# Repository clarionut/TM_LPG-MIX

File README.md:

# TM_LPG-MIX

This repository provides a KiCad schematic and PCB layout for a variant of the TM-LPG-X expander (https://github.com/morganmcw/TM-LPG-X) and the orignal Turing Machine Vactrol Mix expander (https://github.com/TomWhitwell/TuringMixExpander).

It includes the variation switches of the TM-LPG-X, but can be built using capacitors (LPG), resistors (Mix) or with a pin header to allow switching between LPG or Mix mode via a front panel switch (with the resistors and capacitors mounted on the switch).

In their original forms an LPG module would be connected to the Turing Machine PULSES header and a Mix module to the GATES header. This design includes a daughter board which allows both headers to be connected simultaneously. The active connection is selected by a switch or a gate voltage input (the gate input is only active when the switch is OFF).

Taken together, these features allow the unit to be built as a TM-LPG-X, a Turing Machine Vactrol Mix with variation switches, or as a fully configurable combination of the two. Experience since first completing this project has shown that the combination of home made vactrols (https://www.thingiverse.com/thing:6178403) using ultrabright red LEDs and GL5528 LDRs with 220nF capacitors for C5 and C6 leads to such a rapid decay time that the low-pass gate effect is essentially inaudible, though it is visible on an oscilloscope. Reducing the value of these capacitors to 10nF gives a decay time in the region of 0.5 - 1 second which is much more suitable for an LPG. In a similar way, the decay time in Mix mode can be increased by using resistors with a value greater than 10k in place of the capacitors. E.g. 47k resistors in Mix mode give a similar decay time to the 10nF capacitors in LPG mode. A very interesting further extension is to use a dual resistor (5k) / potentiometer (50k) combination in place of the fixed 'Mix' resistors, and a 2-pole 3- or 4-way switch to select the LPG capacitor values (e.g. 100, 33, 10 & 4.7nF) in order to make the decay time adjustable in both modes. I've now tested this ehancement and it is very much worthwhile. I used the resistor and capacitor values shown, but different values may work better depending on the characteristics of the vactrols used.

The PCB layout file uses a custom footprint for the vactrols and a custom model for the 3D viewer. There are included in the TM_LPG-MIX folder - you will have to move them to appropriate locations and tell KiCad where to find them. The PCB design is intended to be processed using the kicad-round-tracks add-on (https://github.com/mitxela/kicad-round-tracks). The schematic also includes a custom audio jack symbol, so I've included both the cache-lib file for the project and a copy of my customised symbols lbrary.

This design is Creative Commons Licensed by Chris Earnshaw: CC-BY-SA - inherited from the parent designs.

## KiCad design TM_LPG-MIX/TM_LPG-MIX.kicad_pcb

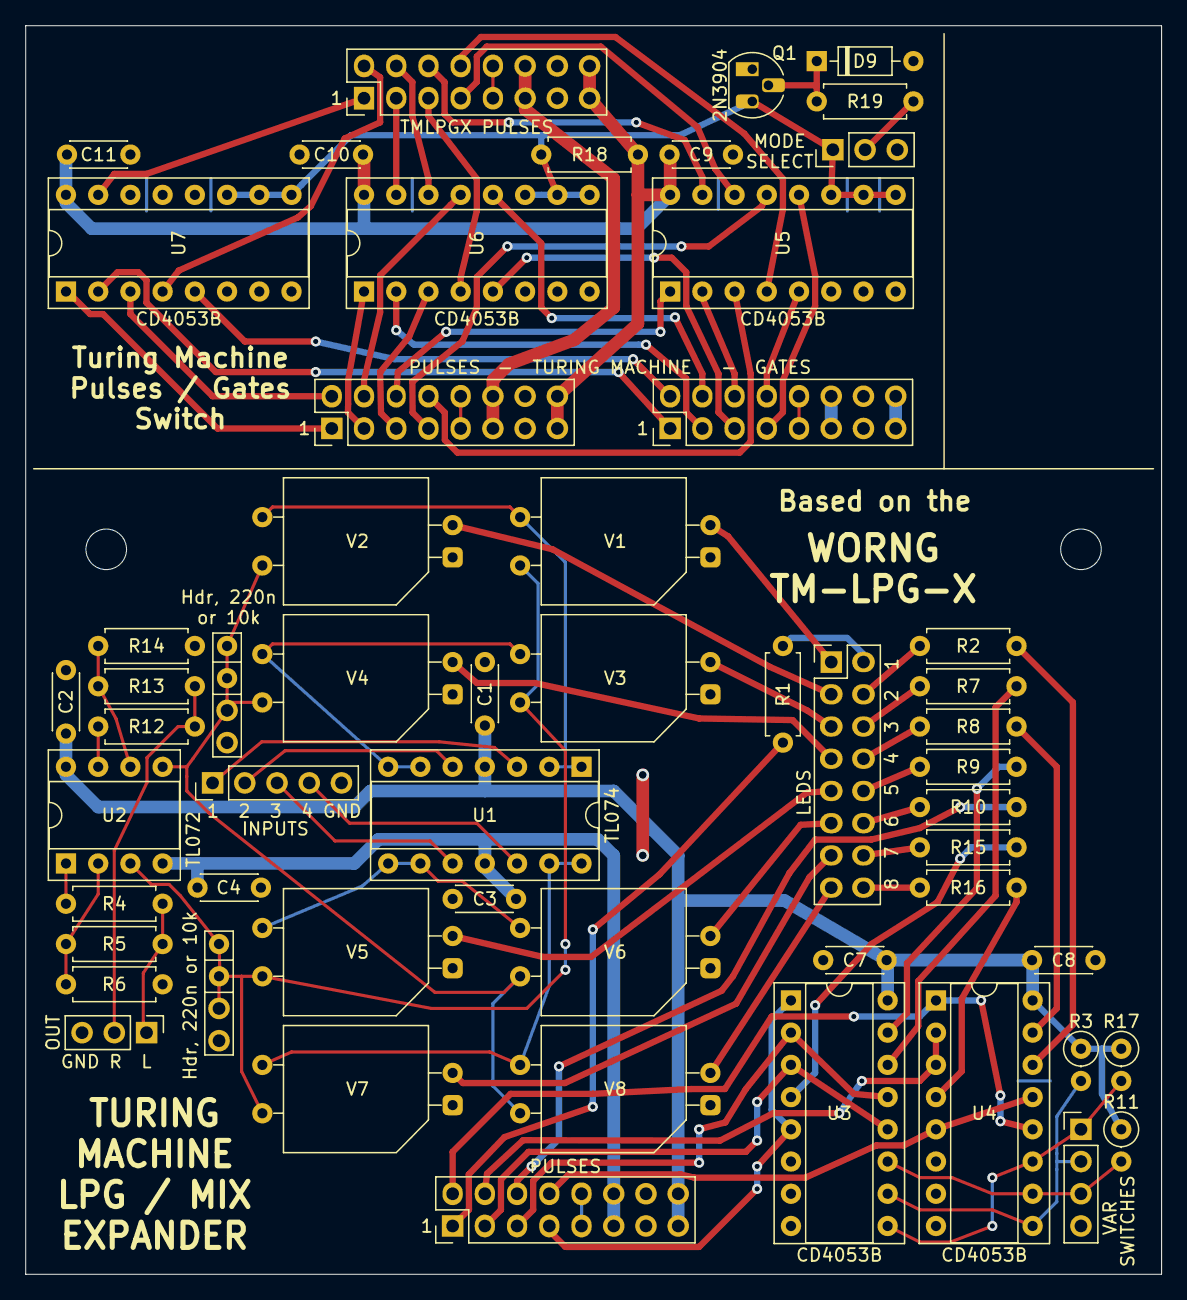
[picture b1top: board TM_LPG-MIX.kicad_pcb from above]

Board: 2 copper layers, 89.5 x 98.4 mm, 56 parts (1 on the bottom side), 88 nets.

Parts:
C1, C2, C3, C4, C7, C8, C9, C10, C11: 100n; C_Disc_D4.3mm_W1.9mm_P5.00mm
C5, C6: 220n; C_Rect_L7.0mm_W2.0mm_P5.00mm
D9: 1N914; D_DO-35_SOD27_P7.62mm_Horizontal
J1: SWITCHES; PinHeader_1x04_P2.54mm_Vertical
J2: AUDIO_IN; PinHeader_1x05_P2.54mm_Vertical
J3: OUT; PinHeader_1x03_P2.54mm_Vertical
J4: LEDS; PinHeader_2x08_P2.54mm_Vertical
J5, J8: PULSES; PinHeader_2x08_P2.54mm_Vertical
J6: TO_TMLPG; PinSocket_2x08_P2.54mm_Vertical
J7: GATES; PinHeader_2x08_P2.54mm_Vertical
J9: MODE; PinHeader_1x03_P2.54mm_Vertical
Q1: 2N3904; TO-92_HandSolder
R1, R2, R7, R8, R9, R10, R15, R16: 2k; R_Axial_DIN0207_L6.3mm_D2.5mm_P7.62mm_Horizontal
R3, R11, R17: 100k; R_Axial_DIN0207_L6.3mm_D2.5mm_P2.54mm_Vertical
R4, R12: 470R; R_Axial_DIN0207_L6.3mm_D2.5mm_P7.62mm_Horizontal
R5, R13, R19: 47k; R_Axial_DIN0207_L6.3mm_D2.5mm_P7.62mm_Horizontal
R6, R14: 10k; R_Axial_DIN0207_L6.3mm_D2.5mm_P7.62mm_Horizontal
R18: 100k; R_Axial_DIN0207_L6.3mm_D2.5mm_P7.62mm_Horizontal
U1: TL074; DIP-14_W7.62mm_Socket
U2: TL072; DIP-8_W7.62mm_Socket
U3, U4, U5, U6, U7: CD4053B; DIP-16_W7.62mm_Socket
V1, V2, V3, V4, V5, V6, V7, V8: VTL5C; CGE_vactrol

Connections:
+12V: C1.2, C2.2, C7.2, C8.2, J5.15, J5.16, R3.1, R11.1, R17.1, U1.4, U2.8, U3.16, U4.16
+12VA: C9.2, C10.2, C11.2, J6.15, J6.16, J8.15, J8.16, R18.1, U5.16, U6.16, U7.16
-12V: C3.2, C4.2, J5.11, J5.12, U1.11, U2.4
-12VA: J6.11, J6.12, J8.11, J8.12
/BUF1: U1.1, U1.2, V1.4, V2.4
/BUF2: U1.6, U1.7, V3.4, V4.4
/BUF3: U1.8, U1.9, V5.4, V6.4
/BUF4: U1.13, U1.14, V7.4, V8.4
/CLK: J5.9, J5.10
/GatesOrPulses/+12VG: J7.15, J7.16
/GatesOrPulses/-12VG: J7.11, J7.12
/GatesOrPulses/CKG: J7.9, J7.10
/GatesOrPulses/CKP: J8.9, J8.10
/GatesOrPulses/CLK: J6.9, J6.10
/GatesOrPulses/GATE1: J7.1, U7.2
/GatesOrPulses/GATE2: J7.2, U7.5
/GatesOrPulses/GATE3: J7.3, U6.2
/GatesOrPulses/GATE4: J7.4, U6.12
/GatesOrPulses/GATE5: J7.5, U6.5
/GatesOrPulses/GATE6: J7.6, U5.2
/GatesOrPulses/GATE7: J7.7, U5.12
/GatesOrPulses/GATE8: J7.8, U5.5
/GatesOrPulses/MODECV: J9.2, R19.2
/GatesOrPulses/MODESW: J9.1, Q1.3, R18.2, U5.9, U5.10, U5.11, U6.9, U6.10, U6.11, U7.9, U7.10, U7.11
/GatesOrPulses/P1: J6.1, U7.15
/GatesOrPulses/P2: J6.2, U7.4
/GatesOrPulses/P3: J6.3, U6.15
/GatesOrPulses/P4: J6.4, U6.14
/GatesOrPulses/P5: J6.5, U6.4
/GatesOrPulses/P6: J6.6, U5.15
/GatesOrPulses/P7: J6.7, U5.14
/GatesOrPulses/P8: J6.8, U5.4
/GatesOrPulses/PLS1: J8.1, U7.1
/GatesOrPulses/PLS2: J8.2, U7.3
/GatesOrPulses/PLS3: J8.3, U6.1
/GatesOrPulses/PLS4: J8.4, U6.13
/GatesOrPulses/PLS5: J8.5, U6.3
/GatesOrPulses/PLS6: J8.6, U5.1
/GatesOrPulses/PLS7: J8.7, U5.13
/GatesOrPulses/PLS8: J8.8, U5.3
/IN1: J2.1, U1.3
/IN2: J2.2, U1.5
/IN3: J2.3, U1.10
/IN4: J2.4, U1.12
/LD1A: J4.2, R1.1
/LD1B: J4.1, V1.2
/LD2A: J4.4, R2.1
/LD2B: J4.3, V2.2
/LD3A: J4.6, R7.1
/LD3B: J4.5, V3.2
/LD4A: J4.8, R8.1
/LD4B: J4.7, V4.2
/LD5A: J4.10, R9.1
/LD5B: J4.9, V5.2
/LD6A: J4.12, R10.1
/LD6B: J4.11, V6.2
/LD7A: J4.14, R15.1
/LD7B: J4.13, V7.2
/LD8A: J4.16, R16.1
/LD8B: J4.15, V8.2
/OUTL: J3.1, R4.2, R5.1
/OUTR: J3.2, R12.2, R13.1
/PULS1: J5.1, R1.2
/PULS2: J5.2, U4.1, U4.12
/PULS3: J5.3, U3.3, U3.12
/PULS4: J5.4, U4.2, U4.3
/PULS5: J5.5, U3.2, U3.13
/PULS6: J5.6, R10.2
/PULS7: J5.7, U3.1, U3.5
/PULS8: J5.8, U4.5, U4.13
/SUML: C5.2, U2.3, V1.3, V3.3, V5.3, V7.3
/SUMR: C6.2, U2.5, V2.3, V4.3, V6.3, V8.3
/SW1: J1.1, R17.2, U3.9, U4.11
/SW2: J1.2, R3.2, U3.10, U4.9
/SW3: J1.3, R11.2, U3.11, U4.10
/TRIG2: R2.2, U4.14
/TRIG3: R7.2, U3.14
/TRIG4: R8.2, U4.15
/TRIG5: R9.2, U3.15
/TRIG7: R15.2, U3.4
/TRIG8: R16.2, U4.4
GND: C1.1, C2.1, C3.1, C4.1, C5.1, C6.1, C7.1, C8.1, J1.4, J2.5, J3.3, J5.13, J5.14, R6.2, R14.2, U3.6, U3.7, U3.8, U4.6, U4.7, U4.8, V1.1, V2.1, V3.1, V4.1, V5.1, V6.1, V7.1, V8.1
GNDA: C9.1, C10.1, C11.1, D9.2, J6.13, J6.14, J7.13, J7.14, J8.13, J8.14, J9.3, Q1.1, U5.6, U5.7, U5.8, U6.6, U6.7, U6.8, U7.6, U7.7, U7.8, U7.12, U7.13
unnamed: D9.1, Q1.2, R19.1
unnamed: R4.1, U2.1
unnamed: R5.2, R6.1, U2.2
unnamed: R12.1, U2.7
unnamed: R13.2, R14.1, U2.6

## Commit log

2023-09-24 Create temp
